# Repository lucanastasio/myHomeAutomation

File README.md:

# myHomeAutomation
Home automation stuff

## Hardware

- Dimmer: LED APA102-2020, 4 PWM ch.
- Central: 4 PWM ch., radar UART, air valve 4 pin

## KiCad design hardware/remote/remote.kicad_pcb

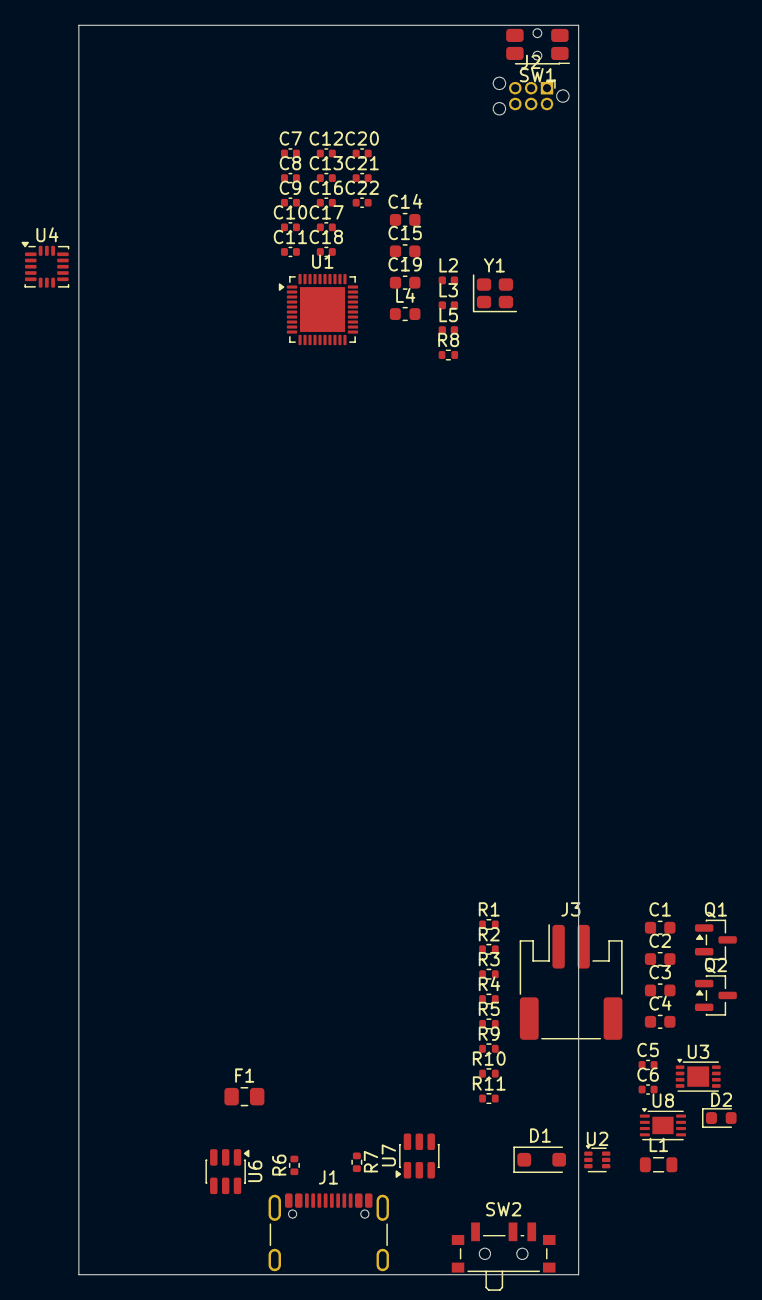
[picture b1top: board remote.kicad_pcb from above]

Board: 2 copper layers, 40.0 x 100.0 mm, 57 parts (1 on the bottom side), 38 nets, no tracks yet.

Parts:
C1: 10u; C_0603_1608Metric
C2, C3, C4, C14, C15, C19: 4.7u; C_0603_1608Metric
C5, C11, C20: 1u; C_0402_1005Metric
C6: 10n; C_0402_1005Metric
C7, C8: 12p; C_0402_1005Metric
C9: 1p; C_0402_1005Metric
C10: 1.2p; C_0402_1005Metric
C12: 47n; C_0402_1005Metric
C13: DNP; C_0402_1005Metric
C16, C21, C22: 100n; C_0402_1005Metric
C17: 100p; C_0402_1005Metric
C18: 820p; C_0402_1005Metric
D1: PMEG1030EH; D_SOD-123F
D2: LED; LED_0603_1608Metric
DS1: OLED-128O064D
F1: Fuse; Fuse_0805_2012Metric_Pad1.15x1.40mm_HandSolder
J1: USB_C_Receptacle_USB2.0_16P; USB_C_Receptacle_GCT_USB4105-xx-A_16P_TopMnt_Horizontal
J2: Conn_ARM_SWD_TagConnect_TC2030-NL; Tag-Connect_TC2030-IDC-NL_2x03_P1.27mm_Vertical
J3: Conn_01x02_MountingPin; JST_PH_S2B-PH-SM4-TB_1x02-1MP_P2.00mm_Horizontal
L1: 1u; L_0805_2012Metric
L2: 4.7n; L_0402_1005Metric
L3: 2.2n; L_0402_1005Metric
L4: 10u; L_0603_1608Metric
L5: 15n; L_0402_1005Metric
Q1: AO3401A; SOT-23
Q2: BSS138; SOT-23
R1, R5: 133k; R_0402_1005Metric
R2, R8, R9, R11: 10k; R_0402_1005Metric
R3, R10: 1k; R_0402_1005Metric
R4: 150; R_0402_1005Metric
R6, R7: 5.1k; R_0402_1005Metric
SW1: SW_Push; SW_SPST_EVQP7C
SW2: SW_SPDT; SW_SPDT_PCM12
U1: nRF52820-QDxx; QFN-40-1EP_5x5mm_P0.4mm_EP3.6x3.6mm
U2: TPS628438DRL; SOT-563
U3: MAX17043; Maxim_WSON-8-1EP_3x2mm_P0.5mm_EP1.75x1.63mm
U4: ADXL363; Analog_LGA-16_3.25x3mm_P0.5mm_LayoutBorder3x5y
U6, U7: USBLC6-2SC6; SOT-23-6
U8: MCP73832-2-MC; DFN-8-1EP_3x2mm_P0.5mm_EP1.7x1.4mm
Y1: 32MHz; Crystal_SMD_2520-4Pin_2.5x2.0mm

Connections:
+1V2: C11.1, C12.1, C13.1, L5.2, U1.26 (DEC6), U1.38 (DEC4)
+3V0: C1.1, C15.1, C20.1, C21.1, C22.1, J2.1 (VCC), L1.2, Q2.1 (G), R4.1, R8.1, R9.1, U1.8 (VDD), U1.9 (VDDH), U1.18 (VDD), U1.30 (VDD), U1.40 (VDD), U2.6 (VOS), U7.5 (VBUS)
+BATT: C4.1, J3.1, Q1.3 (D), R3.1, U8.3 (V_{BAT}), U8.4 (V_{BAT})
/MCU/ANT0: C10.1, L2.1, L3.2
/MCU/ANT1: C9.1, L2.2, U1.24 (ANT)
/MCU/D+: U1.13 (D+), U6.1 (I/O1)
/MCU/D-: U1.12 (D-), U6.3 (I/O2)
/MCU/DCC: L4.1, U1.39 (DCC)
/MCU/DEC1: C16.1, U1.1 (DEC1)
/MCU/DEC3: C17.1, U1.27 (DEC3)
/MCU/DEC5: C18.1, U1.21 (DEC5)
/MCU/DECU: C19.1, U1.11 (DECUSB)
/MCU/SWC: J2.4 (SWCLK), U1.20 (SWDCLK), U7.6 (I/O1)
/MCU/SWD: J2.2 (SWDIO), U1.19 (SWDIO), U7.4 (I/O2)
/MCU/XC1: C8.1, U1.28 (XC1), Y1.1
/MCU/XC2: C7.1, U1.29 (XC2), Y1.4
/MCU/~RST: J2.3 (~RESET), R8.2, SW1.1, U1.16 (P0.18/~RESET)
/PWR/CELL: C5.1, R3.2, U3.2 (CELL)
/PWR/EN: SW2.2 (B), U2.4 (EN)
/PWR/PROG: R2.1, R11.1, U8.8 (PROG)
/PWR/STAT: Q2.2 (S), R9.2
/PWR/SW: L1.1, U2.5 (SW)
/PWR/VSET: R1.1, U2.3 (VSET)
/USB/CC1: J1.A5 (CC1), R6.1
/USB/CC2: J1.B5 (CC2), R7.2
/USB/SBU1: J1.A8 (SBU1), U7.1 (I/O1)
/USB/SBU2: J1.B8 (SBU2), U7.3 (I/O2)
/USB/UD+: J1.A6 (D+), U6.6 (I/O1)
/USB/UD-: J1.A7 (D-), U6.4 (I/O2)
/USB/VUSB: F1.1, J1.A4 (VBUS), J1.A9 (VBUS), J1.B4 (VBUS), J1.B9 (VBUS)
GND: C1.2, C2.2, C3.2, C4.2, C5.2, C6.1, C7.2, C8.2, C9.2, C10.2, C11.2, C12.2, C13.2, C14.2, C15.2, C16.2, C17.2, C18.2, C19.2, C20.2, C21.2, C22.2, J1.A1 (GND), J1.A12 (GND), J1.B1 (GND), J1.B12 (GND), J2.5 (GND), J3.2, R1.2, R2.2, R5.2, R6.2, R7.1, R11.2, SW1.2, SW2.3 (C), U1.25 (VSS_PA), U1.37 (VSS), U1.41 (VSS), U2.1 (GND), U3.1 (CTG), U3.4 (GND), U3.9 (EP), U4.12 (GND), U4.13 (GND), U4.16 (GND), U6.2 (GND), U7.2 (GND), U8.6 (V_{SS}), Y1.2 (G), Y1.3 (G)
unnamed: D2.2 (A), R10.2
unnamed: D2.1 (K), Q2.3 (D), U8.5 (STAT)
unnamed: DS1.1 (GND), DS1.30 (GND)
unnamed: L4.2, L5.1
unnamed: C6.2, R4.2, U3.3 (VDD)
VBUS: C3.1, C14.1, D1.2 (A), F1.2, Q1.1 (G), R5.1, R10.1, U1.10 (VBUS), U6.5 (VBUS), U8.1 (V_{DD}), U8.2 (V_{DD})
VCC: C2.1, D1.1 (K), Q1.2 (S), SW2.1 (A), U2.2 (VIN)

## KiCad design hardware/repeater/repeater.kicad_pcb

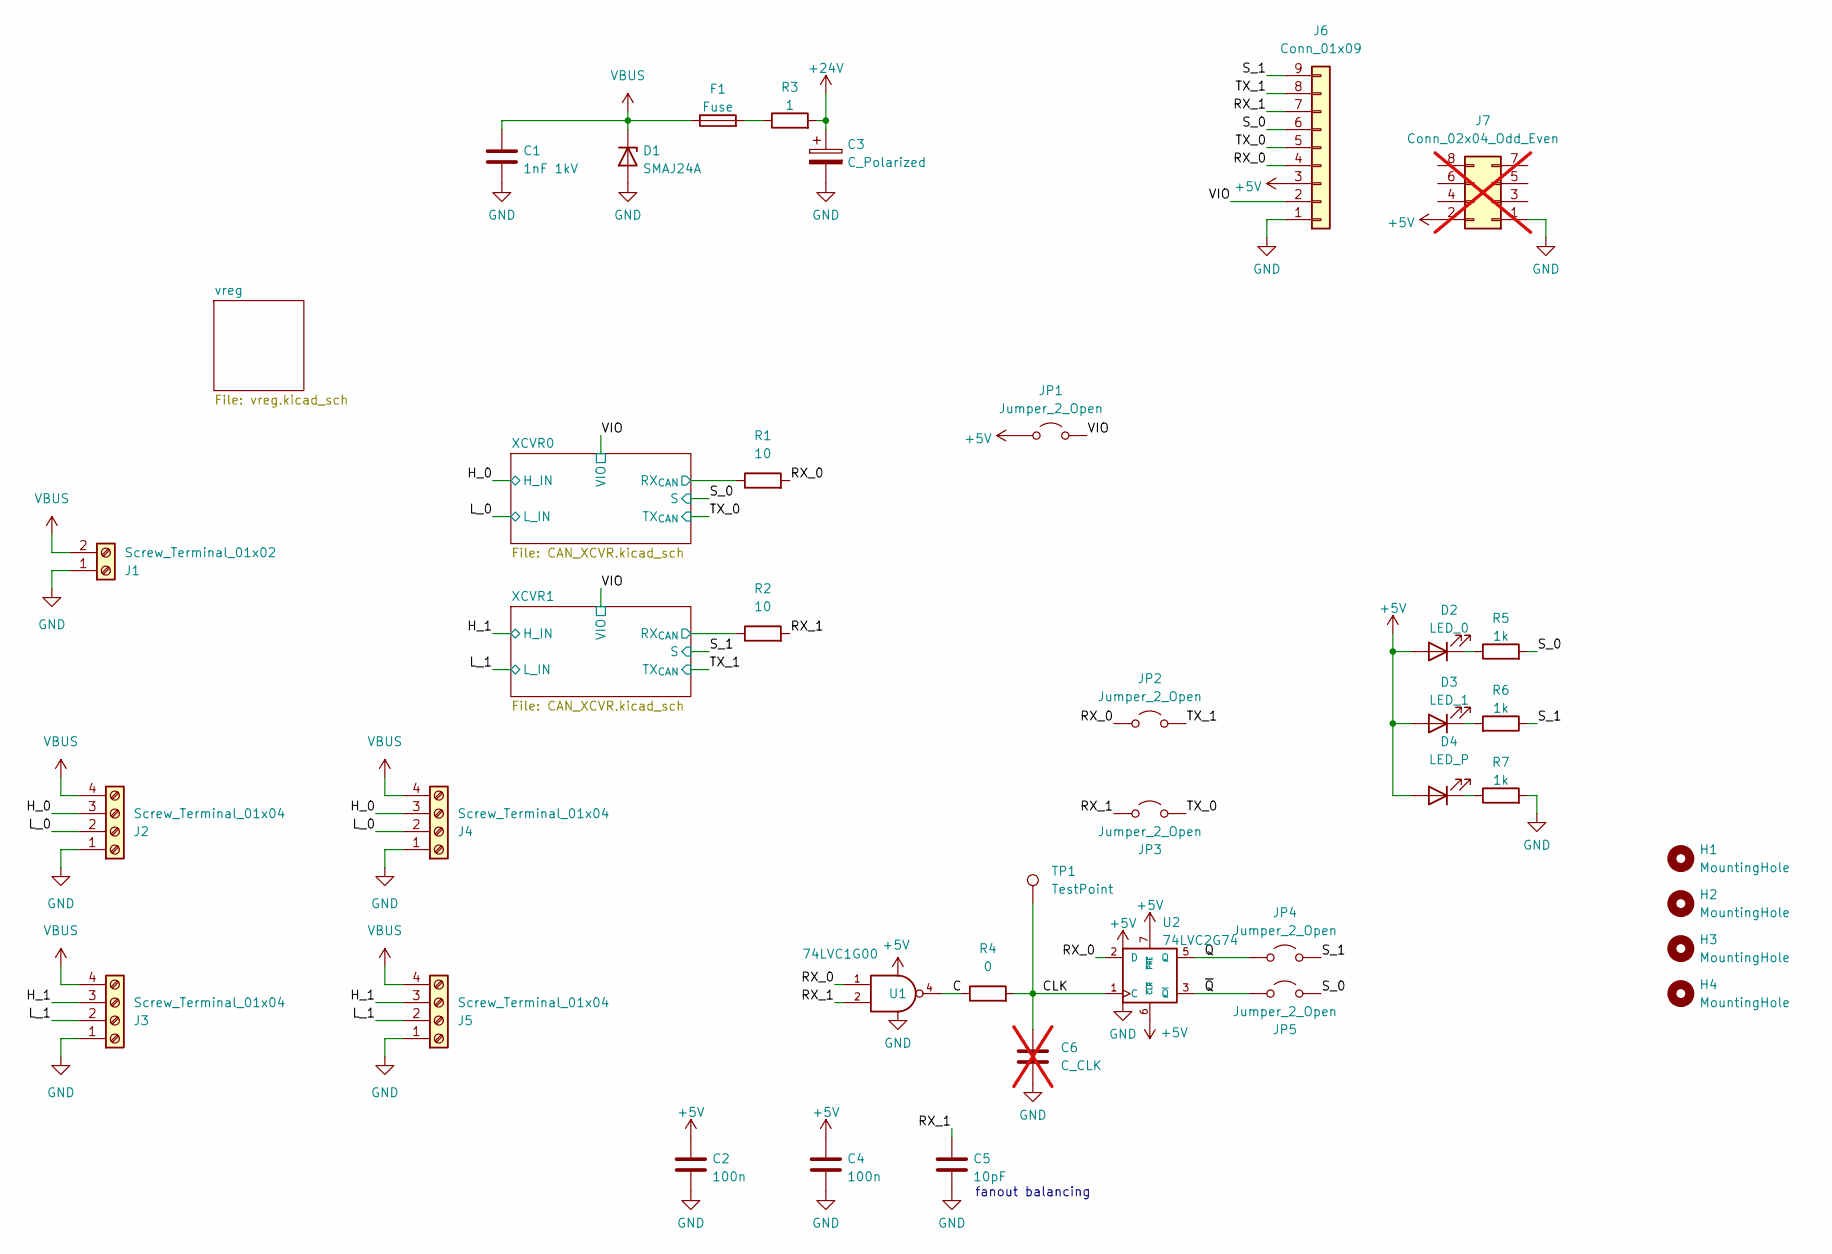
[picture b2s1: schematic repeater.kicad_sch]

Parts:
C1: 1nF 1kV; C_0805_2012Metric_Pad1.18x1.45mm_HandSolder; LCSC C303890
C2, C4: 100n; C_0603_1608Metric; LCSC C14663
C3: C_Polarized; C_Disc_D3.0mm_W1.6mm_P2.50mm
C5: 10pF; C_0603_1608Metric; LCSC C1634
C6: C_CLK; C_0603_1608Metric_Pad1.08x0.95mm_HandSolder; not fitted
D1: SMAJ24A; D_SMA; LCSC C19077541
D2: LED_0; LED_0603_1608Metric_Pad1.05x0.95mm_HandSolder
D3: LED_1; LED_0603_1608Metric_Pad1.05x0.95mm_HandSolder
D4: LED_P; LED_0603_1608Metric_Pad1.05x0.95mm_HandSolder
F1: Fuse; Fuse_0805_2012Metric_Pad1.15x1.40mm_HandSolder; LCSC C41414042
H1, H2, H3, H4: MountingHole; ToolingHole_1.152mm
J1: Screw_Terminal_01x02; PhoenixContact_MSTBA_2,5_2-G_1x02_P5.00mm_Horizontal
J2, J3, J4, J5: Screw_Terminal_01x04; PhoenixContact_MCV_1,5_4-G-3.81_1x04_P3.81mm_Vertical
J6: Conn_01x09; PinHeader_1x09_P2.54mm_Vertical
J7: Conn_02x04_Odd_Even; PinHeader_2x04_P2.54mm_Vertical; not fitted
JP1, JP2, JP3, JP4, JP5: Jumper_2_Open; SolderJumper-2_P1.3mm_Open_RoundedPad1.0x1.5mm
R1, R2: 10; R_0603_1608Metric; LCSC C22859
R3: 1; R_0805_2012Metric; LCSC C25271
R4: 0; R_0603_1608Metric_Pad0.98x0.95mm_HandSolder; LCSC C21189
R5, R6, R7: 1k; R_0603_1608Metric; LCSC C21190
TP1: TestPoint; TestPoint_Loop_D1.80mm_Drill1.0mm_Beaded
U1: 74LVC1G00; SOT-353_SC-70-5; LCSC C2976658
U2: 74LVC2G74; TSSOP-8_3x3mm_P0.65mm; LCSC C1850266

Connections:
+5V: C2.2, C4.2, D2.2 (A), D3.2 (A), D4.2 (A), J6.3, J7.2, JP1.1 (A), U1.5 (VCC), U2.6 (~CLR), U2.7 (~PRE), U2.8 (VCC); also elsewhere on the board
+24V: C3.1, R3.2; also elsewhere on the board
/C: R4.1, U1.4
/CLK: C6.1, R4.2, TP1.1, U2.1 (C)
/H_0: J2.3, J4.3; also elsewhere on the board
/H_1: J3.3, J5.3; also elsewhere on the board
/L_0: J2.2, J4.2; also elsewhere on the board
/L_1: J3.2, J5.2; also elsewhere on the board
/Q: JP4.1 (A), U2.5 (Q)
/RX_0: J6.4, JP2.1 (A), R1.2, U1.1, U2.2 (D)
/RX_1: C5.1, J6.7, JP3.1 (A), R2.2, U1.2
/S_0: J6.6, JP5.2 (B), R5.2; also elsewhere on the board
/S_1: J6.9, JP4.2 (B), R6.1; also elsewhere on the board
/TX_0: J6.5, JP3.2 (B); also elsewhere on the board
/TX_1: J6.8, JP2.2 (B); also elsewhere on the board
/VIO: J6.2, JP1.2 (B); also elsewhere on the board
/XCVR0/RX_{CAN}: R1.1; also elsewhere on the board
/XCVR1/RX_{CAN}: R2.1; also elsewhere on the board
/~Q: JP5.1 (A), U2.3 (~Q)
GND: C1.2, C2.1, C3.2, C4.1, C5.2, C6.2, D1.2 (A), J1.1, J2.1, J3.1, J4.1, J5.1, J6.1, J7.1, R7.2, U1.3 (GND), U2.4 (GND); also elsewhere on the board
unnamed: D2.1 (K), R5.1
unnamed: D3.1 (K), R6.2
unnamed: D4.1 (K), R7.1
unnamed: F1.2, R3.1
VBUS: C1.1, D1.1 (K), F1.1, J1.2, J2.4, J3.4, J4.4, J5.4

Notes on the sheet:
fanout balancing

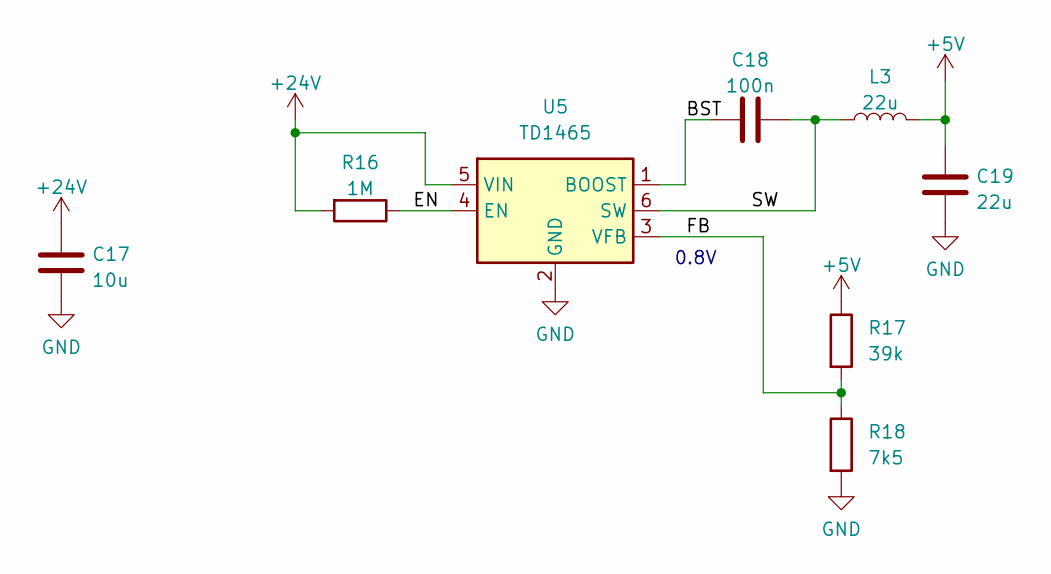
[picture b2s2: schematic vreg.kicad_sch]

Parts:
C17: 10u; C_1206_3216Metric; LCSC C13585
C18: 100n; C_0603_1608Metric; LCSC C14663
C19: 22u; C_0805_2012Metric; LCSC C45783
L3: 22u; L_1210_3225Metric; LCSC C223225
R16: 1M; R_0603_1608Metric; LCSC C22935
R17: 39k; R_0603_1608Metric; LCSC C23153
R18: 7k5; R_0603_1608Metric; LCSC C23234
U5: TD1465; SOT-23-6; LCSC C2832208

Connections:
+5V: C19.2, L3.2, R17.1; also elsewhere on the board
+24V: C17.2, R16.2, U5.5 (VIN); also elsewhere on the board
/vreg/BST: C18.1, U5.1 (BOOST)
/vreg/EN: R16.1, U5.4 (EN)
/vreg/FB: R17.2, R18.1, U5.3 (VFB)
/vreg/SW: C18.2, L3.1, U5.6 (SW)
GND: C17.1, C19.1, R18.2, U5.2 (GND); also elsewhere on the board

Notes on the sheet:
0.8V

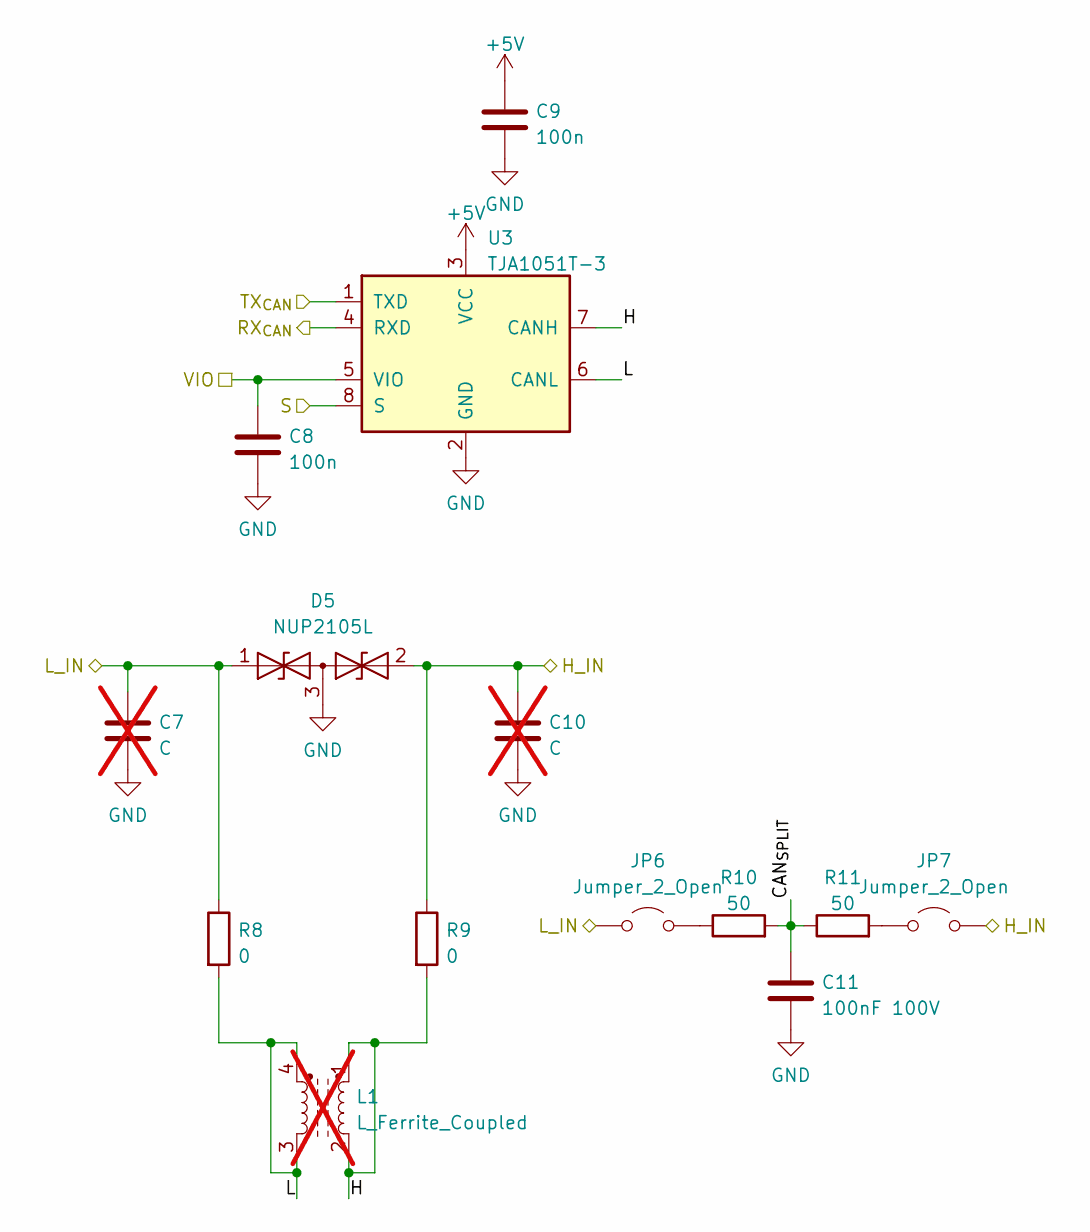
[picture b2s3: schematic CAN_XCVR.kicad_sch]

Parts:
C7, C10: C; C_0603_1608Metric; not fitted
C8, C9: 100n; C_0603_1608Metric; LCSC C14663
C11: 100nF 100V; C_0805_2012Metric_Pad1.18x1.45mm_HandSolder; LCSC C28233
D5: NUP2105L; SOT-23; LCSC C5180311
JP6, JP7: Jumper_2_Open; SolderJumper-2_P1.3mm_Open_RoundedPad1.0x1.5mm
L1: L_Ferrite_Coupled; L_CommonModeChoke_Coilcraft_0805USB; not fitted
R8, R9: 0; R_0603_1608Metric; LCSC C21189
R10, R11: 50; R_0805_2012Metric_Pad1.20x1.40mm_HandSolder; LCSC C17720
U3: TJA1051T-3; SOIC-8_3.9x4.9mm_P1.27mm; LCSC C51954344

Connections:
+5V: C9.2, U3.3 (VCC); also elsewhere on the board
/H_1: C10.1, D5.2 (A2), JP7.2 (B), R9.1; also elsewhere on the board
/L_1: C7.1, D5.1 (A1), JP6.1 (A), R8.1; also elsewhere on the board
/S_1: U3.8 (S); also elsewhere on the board
/TX_1: U3.1 (TXD); also elsewhere on the board
/VIO: C8.2, U3.5 (VIO); also elsewhere on the board
/XCVR1/CAN_{SPLIT}: C11.1, R10.2, R11.1
/XCVR1/H: R9.2, U3.7 (CANH)
/XCVR1/L: R8.2, U3.6 (CANL)
/XCVR1/RX_{CAN}: U3.4 (RXD); also elsewhere on the board
GND: C7.2, C8.1, C9.1, C10.2, C11.2, D5.3 (common), U3.2 (GND); also elsewhere on the board
unnamed: JP6.2 (B), R10.1
unnamed: JP7.1 (A), R11.2

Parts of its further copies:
C12, C15: C; C_0603_1608Metric; not fitted
C16: 100nF 100V; C_0805_2012Metric_Pad1.18x1.45mm_HandSolder; LCSC C28233
D6: NUP2105L; SOT-23; LCSC C5180311
JP8, JP9: Jumper_2_Open; SolderJumper-2_P1.3mm_Open_RoundedPad1.0x1.5mm
R12, R13: 0; R_0603_1608Metric; LCSC C21189
R14, R15: 50; R_0805_2012Metric_Pad1.20x1.40mm_HandSolder; LCSC C17720
U4: TJA1051T-3; SOIC-8_3.9x4.9mm_P1.27mm; LCSC C51954344

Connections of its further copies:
+5V: U4.3 (VCC); also elsewhere on the board
/H_0: C15.1, D6.2 (A2), JP9.2 (B), R13.1; also elsewhere on the board
/L_0: C12.1, D6.1 (A1), JP8.1 (A), R12.1; also elsewhere on the board
/S_0: U4.8 (S); also elsewhere on the board
/TX_0: U4.1 (TXD); also elsewhere on the board
/VIO: U4.5 (VIO); also elsewhere on the board
/XCVR0/CAN_{SPLIT}: C16.1, R14.2, R15.1
/XCVR0/H: R13.2, U4.7 (CANH)
/XCVR0/L: R12.2, U4.6 (CANL)
/XCVR0/RX_{CAN}: U4.4 (RXD); also elsewhere on the board
GND: C12.2, C15.2, C16.2, D6.3 (common), U4.2 (GND); also elsewhere on the board
unnamed: JP8.2 (B), R14.1
unnamed: JP9.1 (A), R15.2

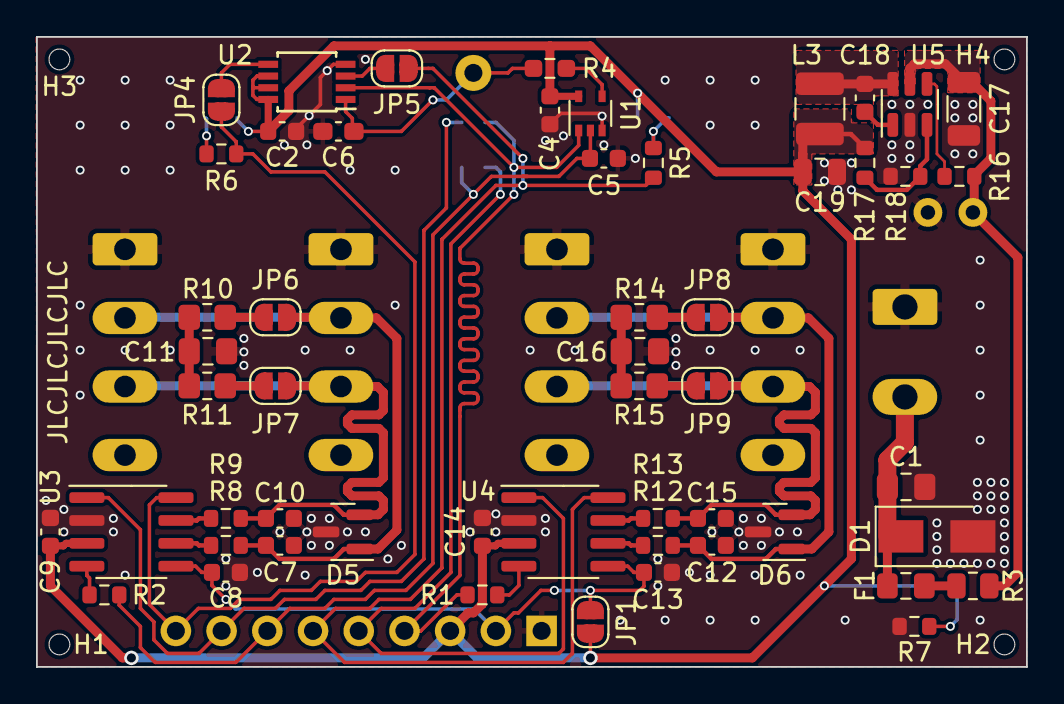
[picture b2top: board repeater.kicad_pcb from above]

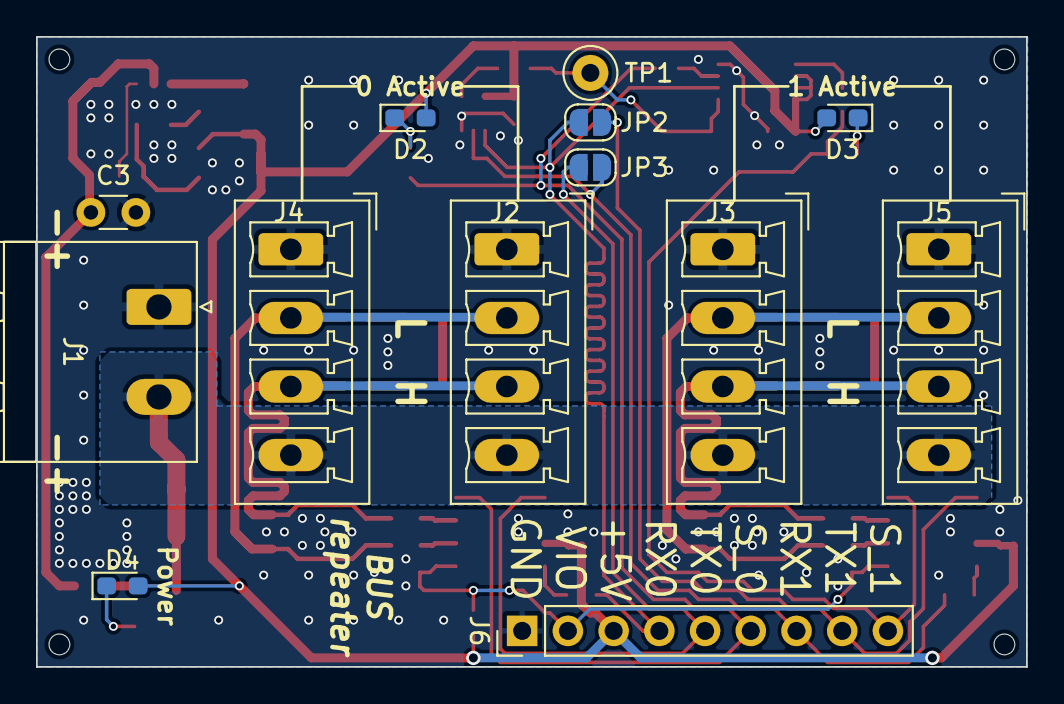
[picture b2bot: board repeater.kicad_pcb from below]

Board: 2 copper layers, 55.0 x 35.0 mm, 70 parts (13 on the bottom side), 39 nets.

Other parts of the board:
C13, C14: 100n; C_0603_1608Metric

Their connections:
+5V: C14.2; also elsewhere on the board
/VIO: C13.2; also elsewhere on the board
GND: C13.1, C14.1; also elsewhere on the board

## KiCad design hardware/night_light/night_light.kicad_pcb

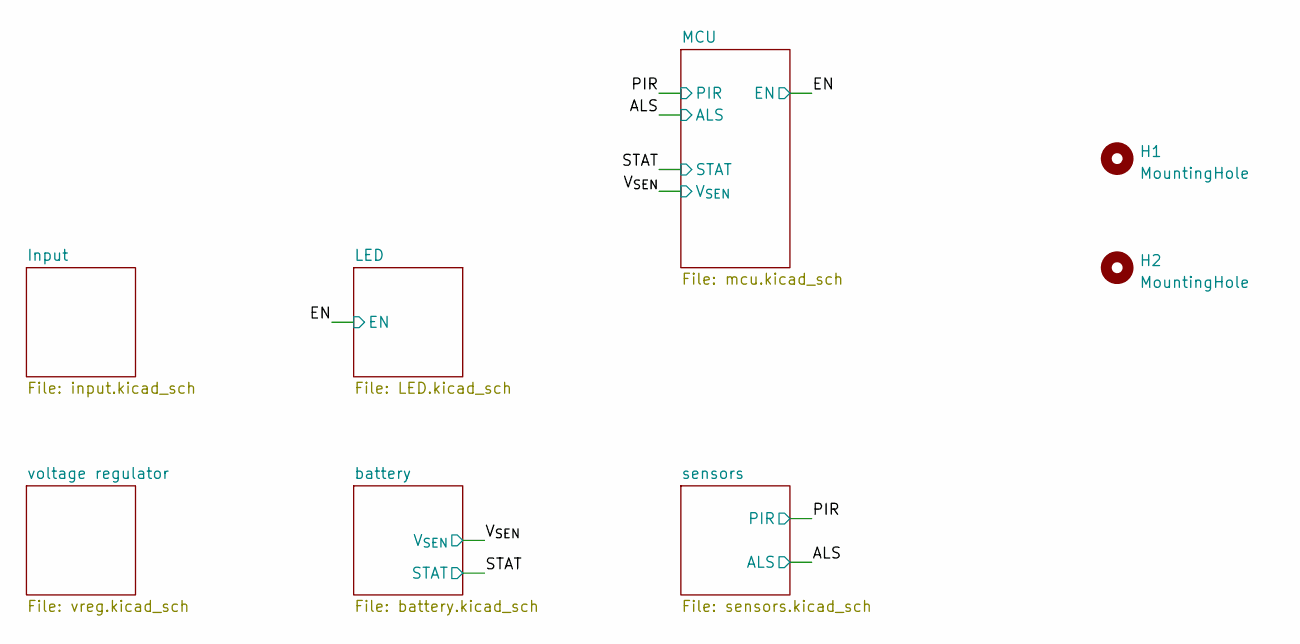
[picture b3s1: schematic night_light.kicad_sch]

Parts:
H1, H2: MountingHole; MountingHole_2.1mm

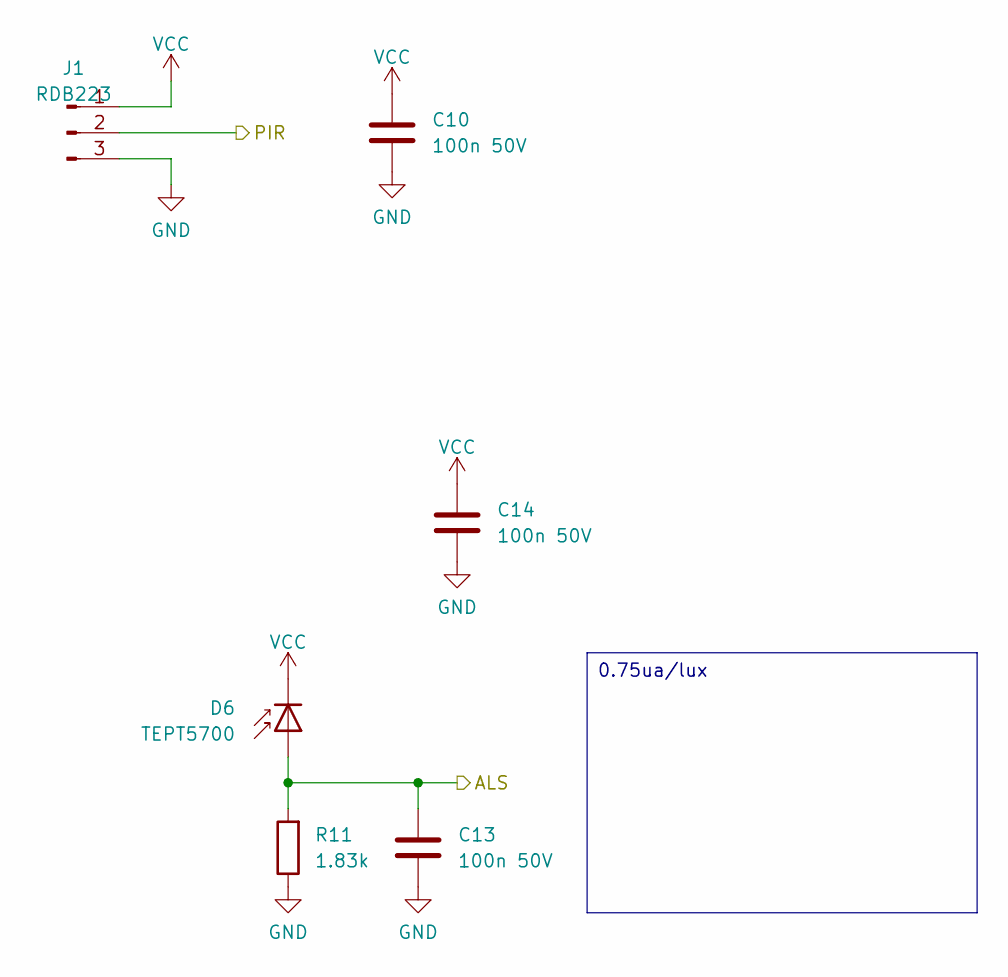
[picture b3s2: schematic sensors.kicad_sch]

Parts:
C10, C13, C14: 100n 50V; C_0603_1608Metric; LCSC C14663
D6: TEPT5700; LED_D3.0mm_FlatTop
J1: RDB223; TO-5-3_Window; LCSC C879408
R11: 1.83k; R_0603_1608Metric

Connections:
/ALS: C13.2, D6.2 (A), R11.2; also elsewhere on the board
/PIR: J1.2; also elsewhere on the board
GND: C10.2, C13.1, C14.2, J1.3, R11.1; also elsewhere on the board
VCC: C10.1, C14.1, D6.1 (K), J1.1; also elsewhere on the board

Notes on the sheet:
0.75ua/lux

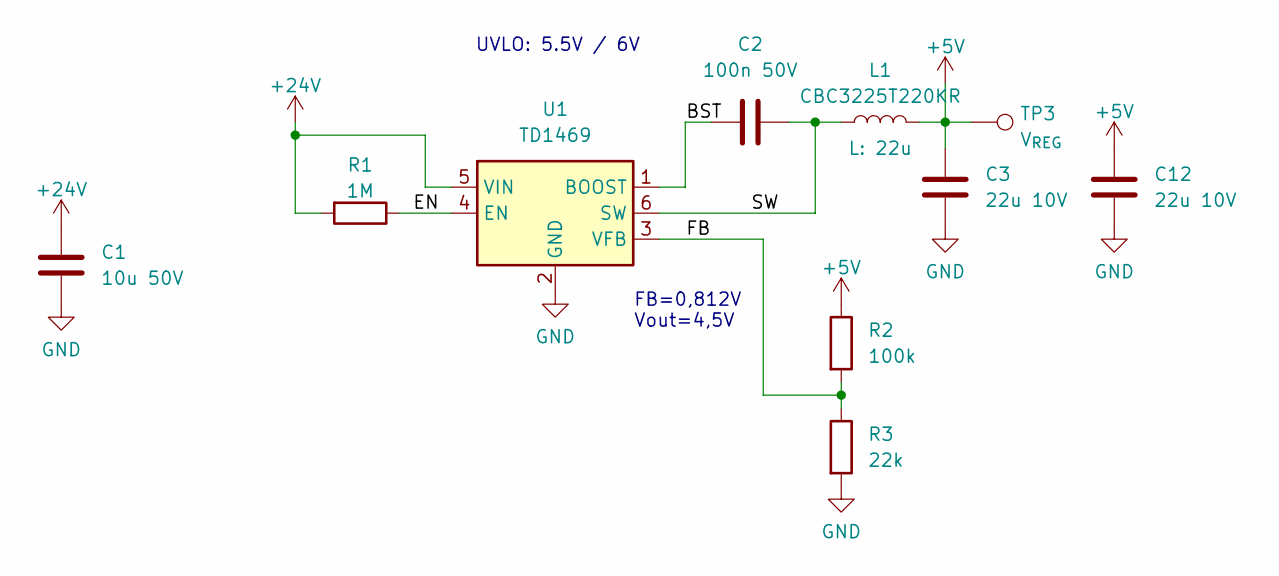
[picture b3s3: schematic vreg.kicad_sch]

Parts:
C1: 10u 50V; C_1206_3216Metric; LCSC C13585
C2: 100n 50V; C_0603_1608Metric; LCSC C14663
C3, C12: 22u 10V; C_0805_2012Metric; LCSC C29277
L1: CBC3225T220KR; L_1210_3225Metric; LCSC C223225
R1: 1M; R_0603_1608Metric; LCSC C22935
R2: 100k; R_0603_1608Metric; LCSC C25803
R3: 22k; R_0603_1608Metric; LCSC C31850
TP3: V_{REG}; TestPoint_THTPad_D1.0mm_Drill0.5mm
U1: TD1469; SOT-23-6; LCSC C2832208

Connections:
+5V: C3.2, C12.2, L1.2, R2.1, TP3.1; also elsewhere on the board
+24V: C1.2, R1.2, U1.5 (VIN); also elsewhere on the board
/voltage regulator/BST: C2.1, U1.1 (BOOST)
/voltage regulator/EN: R1.1, U1.4 (EN)
/voltage regulator/FB: R2.2, R3.1, U1.3 (VFB)
/voltage regulator/SW: C2.2, L1.1, U1.6 (SW)
GND: C1.1, C3.1, C12.1, R3.2, U1.2 (GND); also elsewhere on the board

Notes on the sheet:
FB=0,812V Vout=4,5V
UVLO: 5.5V / 6V

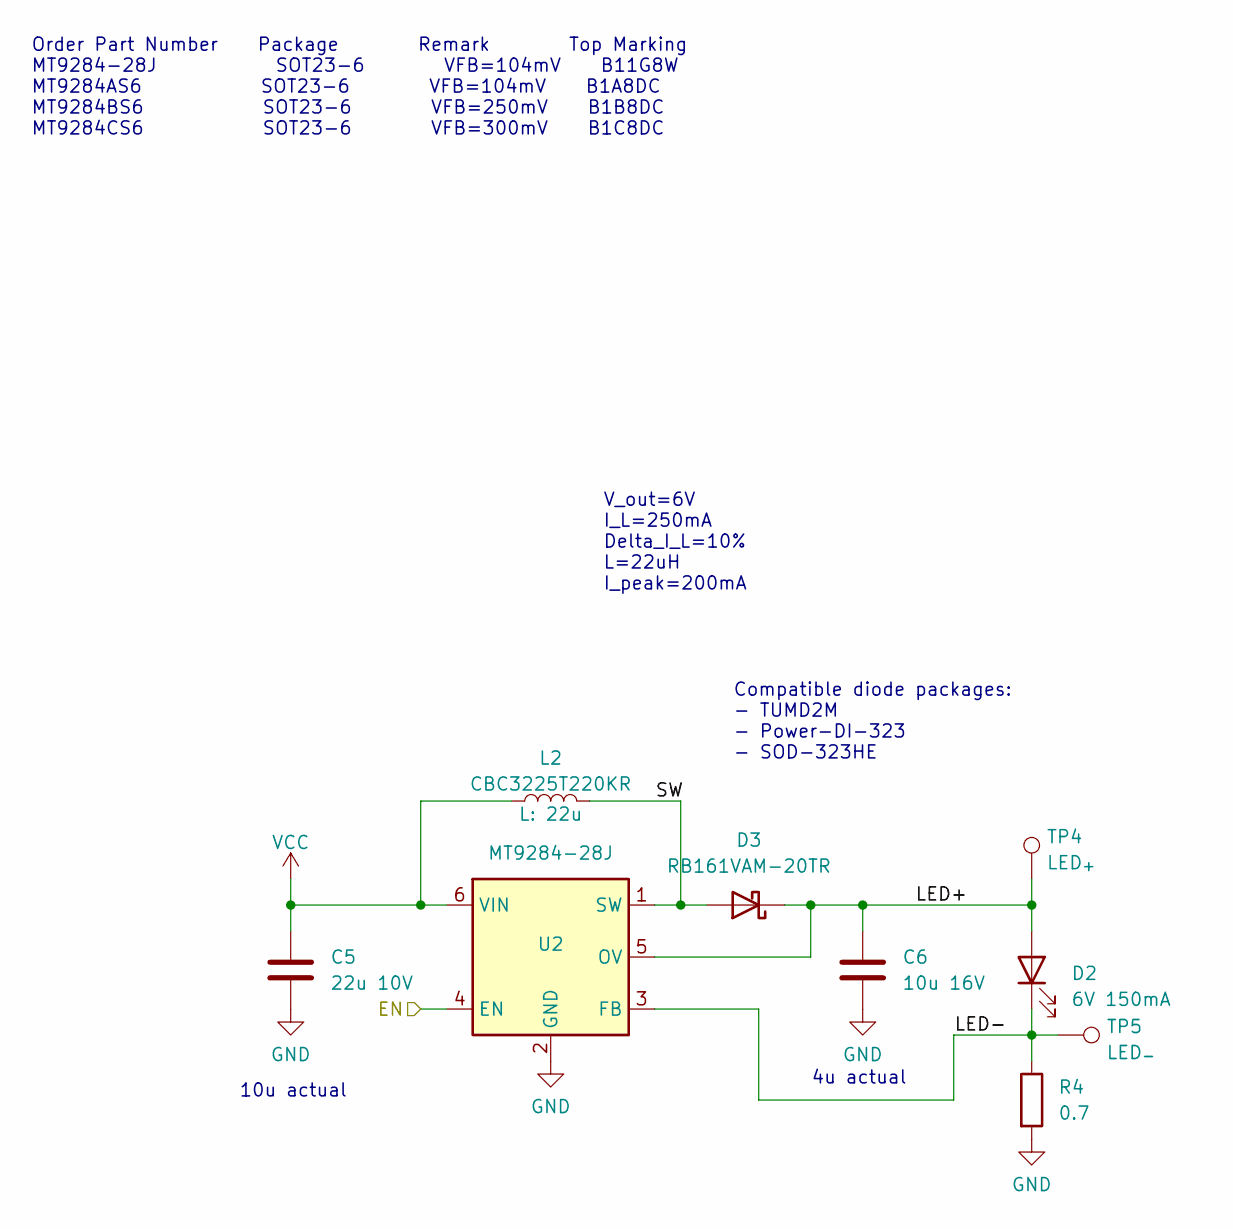
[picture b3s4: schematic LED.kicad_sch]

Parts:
C5: 22u 10V; C_0805_2012Metric; LCSC C29277
C6: 10u 16V; C_0805_2012Metric; LCSC C1713
D2: 6V 150mA; LED_PLCC_2835_Handsoldering
D3: RB161VAM-20TR; D_TUMD2; LCSC C308725
L2: CBC3225T220KR; L_1210_3225Metric; LCSC C223225
R4: 0.7; R_0805_2012Metric; LCSC C175718
TP4: LED_{+}; TestPoint_THTPad_D1.0mm_Drill0.5mm
TP5: LED_{-}; TestPoint_THTPad_D1.0mm_Drill0.5mm
U2: MT9284-28J; TSOT-23-6; LCSC C181780

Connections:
/EN: U2.4 (EN); also elsewhere on the board
/LED/LED+: C6.1, D2.2 (A), D3.1 (K), TP4.1, U2.5 (OV)
/LED/LED-: D2.1 (K), R4.1, TP5.1, U2.3 (FB)
/LED/SW: D3.2 (A), L2.2, U2.1 (SW)
GND: C5.2, C6.2, R4.2, U2.2 (GND); also elsewhere on the board
VCC: C5.1, L2.1, U2.6 (VIN); also elsewhere on the board

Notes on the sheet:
Order Part Number Package Remark Top Marking MT9284-28J SOT23-6 VFB=104mV B11G8W MT9284AS6 SOT23-6 VFB=104mV B1A8DC MT9284BS6 SOT23-6 VFB=250mV B1B8DC MT9284CS6 SOT23-6 VFB=300mV B1C8DC
Compatible diode packages: - TUMD2M - Power-DI-323 - SOD-323HE
V_out=6V I_L=250mA Delta_I_L=10% L=22uH I_peak=200mA
10u actual
4u actual

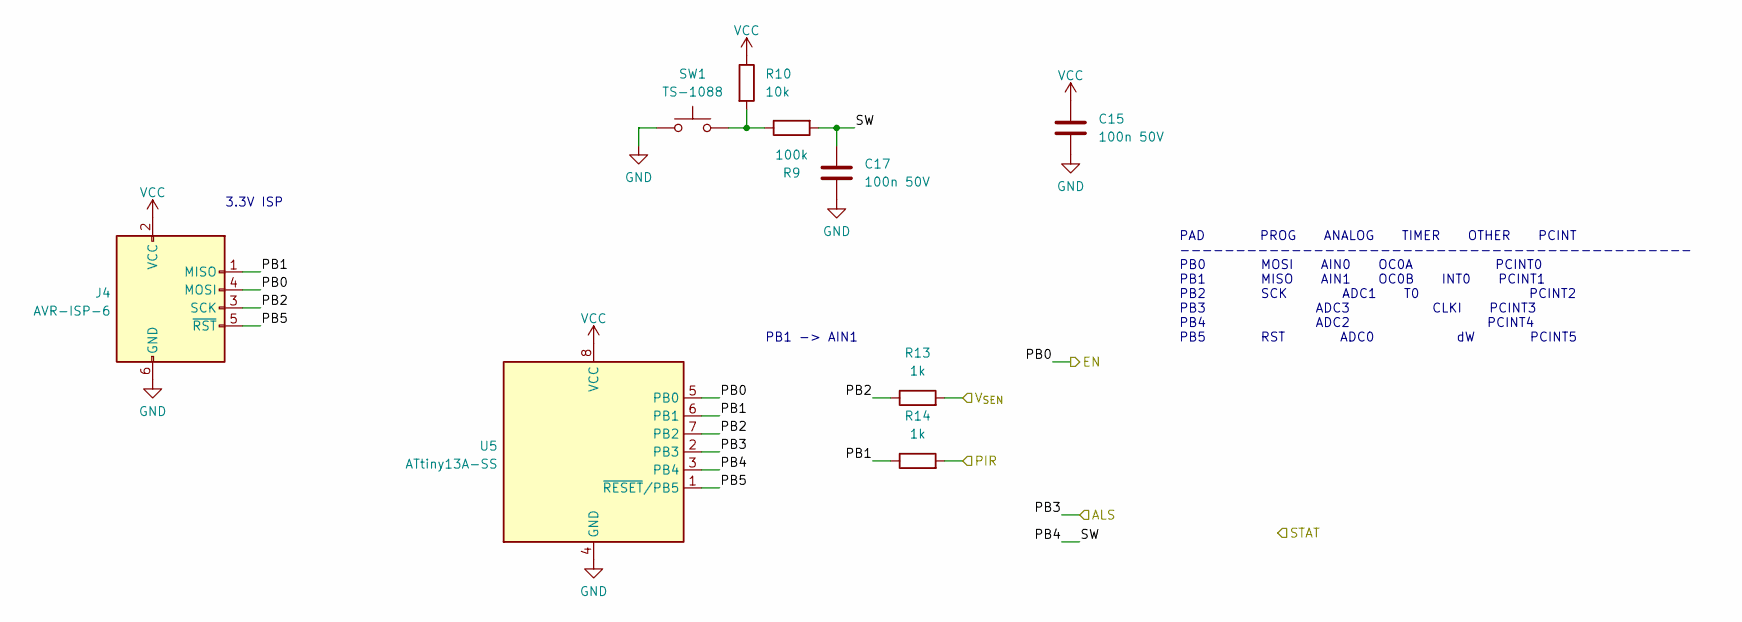
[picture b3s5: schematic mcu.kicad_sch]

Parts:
C15, C17: 100n 50V; C_0603_1608Metric; LCSC C14663
J4: AVR-ISP-6; Tag-Connect_TC2030-IDC-NL_2x03_P1.27mm_Vertical
R9: 100k; R_0603_1608Metric; LCSC C25803
R10: 10k; R_0603_1608Metric; LCSC C25804
R13, R14: 1k; R_0603_1608Metric; LCSC C21190
SW1: TS-1088; SW_Push_SPST_NO_Alps_SKRK; LCSC Part # C455280
U5: ATtiny13A-SS; SOIC-8_3.9x4.9mm_P1.27mm; LCSC C14075

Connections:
/ALS: U5.2 (PB3); also elsewhere on the board
/EN: J4.4 (MOSI), U5.5 (PB0); also elsewhere on the board
/MCU/PB1: J4.1 (MISO), R14.1, U5.6 (PB1)
/MCU/PB2: J4.3 (SCK), R13.1, U5.7 (PB2)
/MCU/PB4: C17.1, R9.2, U5.3 (PB4)
/MCU/PB5: J4.5 (~RST), U5.1 (~RESET/PB5)
/PIR: R14.2; also elsewhere on the board
/V_{SEN}: R13.2; also elsewhere on the board
GND: C15.2, C17.2, J4.6 (GND), SW1.1, U5.4 (GND); also elsewhere on the board
unnamed: R9.1, R10.2, SW1.2
VCC: C15.1, J4.2 (VCC), R10.1, U5.8 (VCC); also elsewhere on the board

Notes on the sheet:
PAD PROG ANALOG TIMER OTHER PCINT ---------------------------------------------- PB0 MOSI AIN0 OC0A PCINT0 PB1 MISO AIN1 OC0B INT0 PCINT1 PB2 SCK ADC1 T0 PCINT2 PB3 ADC3 CLKI PCINT3 PB4 ADC2 PCINT4 PB5 RST ADC0 dW PCINT5
PB1 -> AIN1
3.3V ISP

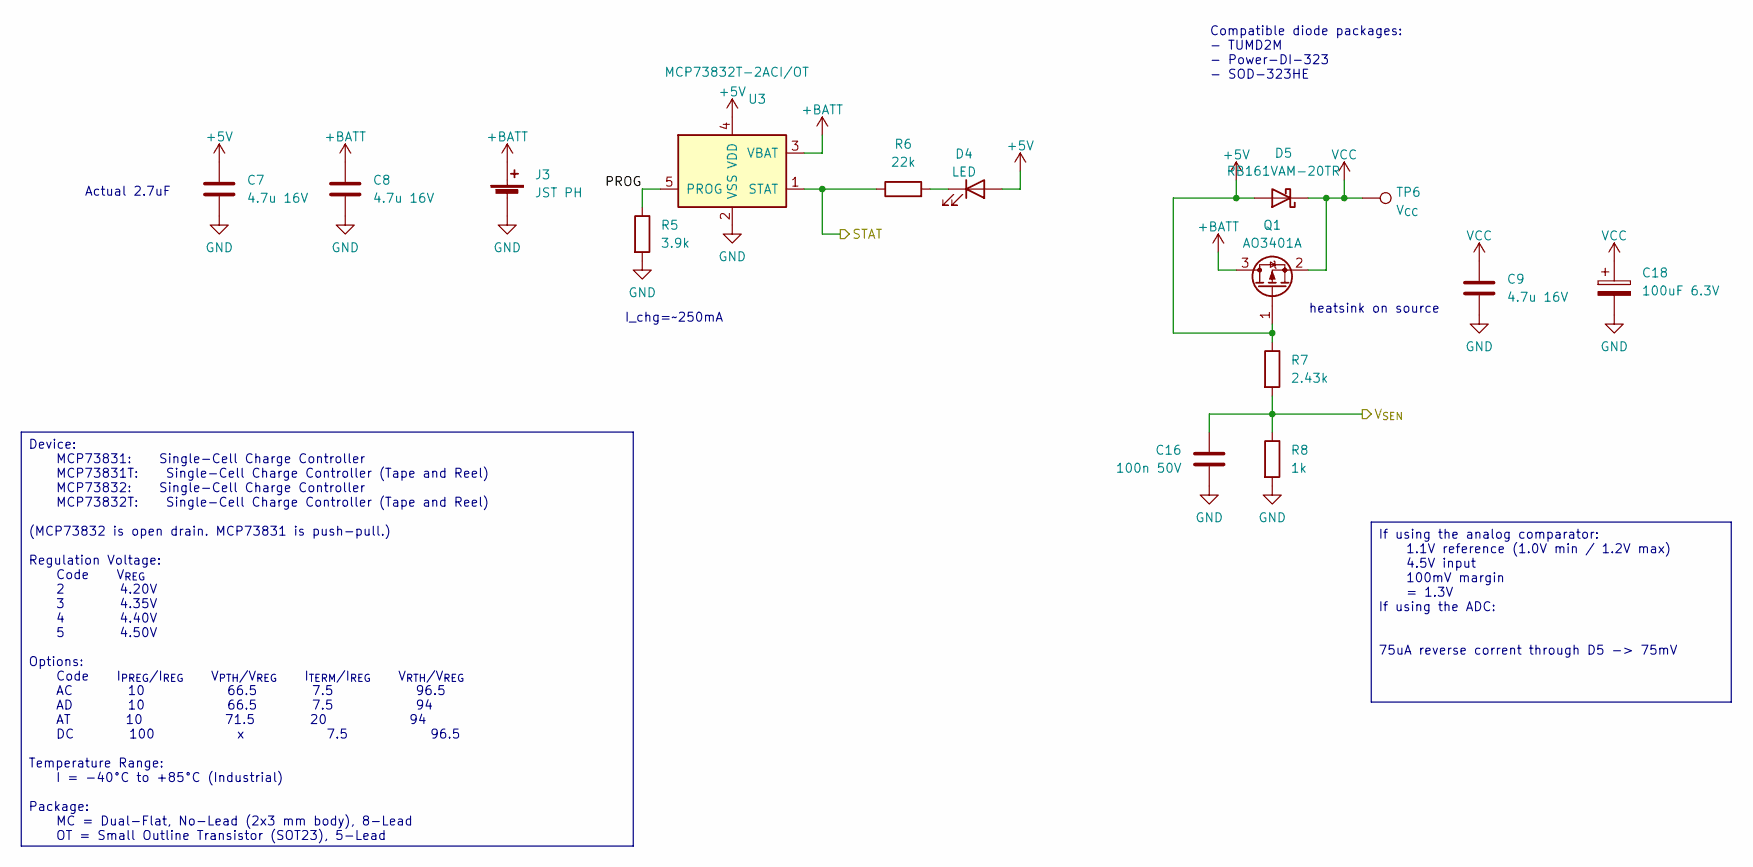
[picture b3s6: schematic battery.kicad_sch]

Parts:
C7, C8, C9: 4.7u 16V; C_0603_1608Metric; LCSC C19666
C16: 100n 50V; C_0603_1608Metric; LCSC C14663
C18: 100uF 6.3V; CP_EIA-3528-15_AVX-H; LCSC C16133
D4: LED; LED_0603_1608Metric_Pad1.05x0.95mm_HandSolder
D5: RB161VAM-20TR; D_TUMD2; LCSC C308725
J3: JST PH; JST_PH_B2B-PH-K_1x02_P2.00mm_Vertical; LCSC Part # C722767
Q1: AO3401A; SOT-23; LCSC C15127
R5: 3.9k; R_0603_1608Metric; LCSC C23018
R6: 22k; R_0603_1608Metric; LCSC C4190
R7: 2.43k; R_0603_1608Metric; LCSC C22906
R8: 1k; R_0603_1608Metric; LCSC C21190
TP6: V_{CC}; TestPoint_THTPad_D1.0mm_Drill0.5mm
U3: MCP73832T-2ACI/OT; SOT-23-5; LCSC C38066

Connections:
+5V: C7.1, D4.2 (A), D5.2 (A), Q1.1 (G), R7.1, U3.4 (VDD); also elsewhere on the board
+BATT: C8.1, J3.1 (+), Q1.3 (D), U3.3 (VBAT)
/STAT: R6.1, U3.1 (STAT)
/V_{SEN}: C16.1, R7.2, R8.1; also elsewhere on the board
/battery/PROG: R5.1, U3.5 (PROG)
GND: C7.2, C8.2, C9.2, C16.2, C18.2, J3.2 (-), R5.2, R8.2, U3.2 (VSS); also elsewhere on the board
unnamed: D4.1 (K), R6.2
VCC: C9.1, C18.1, D5.1 (K), Q1.2 (S), TP6.1; also elsewhere on the board

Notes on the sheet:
Compatible diode packages: - TUMD2M - Power-DI-323 - SOD-323HE
Actual 2.7uF
I_chg=~250mA
heatsink on source
If using the analog comparator: 1.1V reference (1.0V min / 1.2V max) 4.5V input 100mV margin = 1.3V If using the ADC: 75uA reverse corrent through D5 -> 75mV
Device: MCP73831: Single-Cell Charge Controller MCP73831T: Single-Cell Charge Controller (Tape and Reel) MCP73832: Single-Cell Charge Controller MCP73832T: Single-Cell Charge Controller (Tape and Reel) (MCP73832 is open drain. MCP73831 is push-pull.) Regulation Voltage: Code V_{REG} 2 4.20V 3 4.35V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

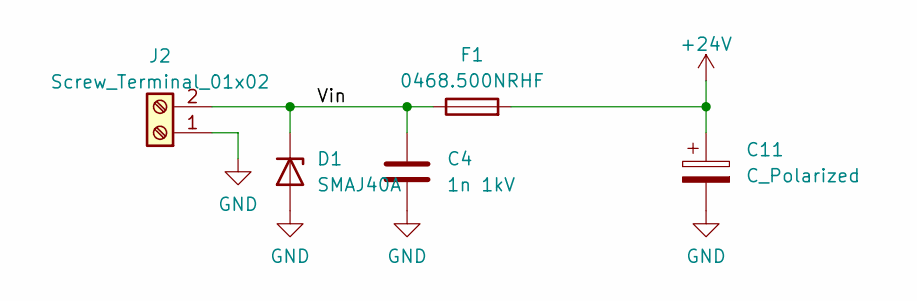
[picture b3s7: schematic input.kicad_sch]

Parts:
C4: 1n 1kV; C_0603_1608Metric; LCSC Part # C696365
C11: C_Polarized; C_Disc_D3.0mm_W1.6mm_P2.50mm
D1: SMAJ40A; D_SMA; LCSC C134985
F1: 0468.500NRHF; Fuse_1206_3216Metric_Pad1.42x1.75mm_HandSolder
J2: Screw_Terminal_01x02; PhoenixContact_MCV_1,5_2-G-3.81_1x02_P3.81mm_Vertical

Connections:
+24V: C11.1, F1.2; also elsewhere on the board
/Input/Vin: C4.1, D1.1 (K), F1.1, J2.2
GND: C4.2, C11.2, D1.2 (A), J2.1; also elsewhere on the board
